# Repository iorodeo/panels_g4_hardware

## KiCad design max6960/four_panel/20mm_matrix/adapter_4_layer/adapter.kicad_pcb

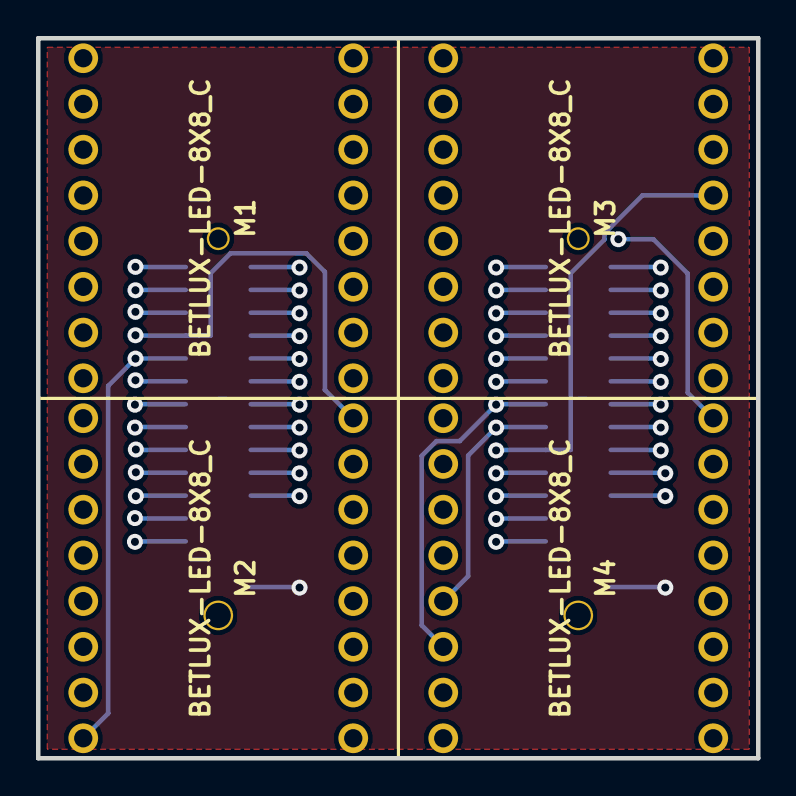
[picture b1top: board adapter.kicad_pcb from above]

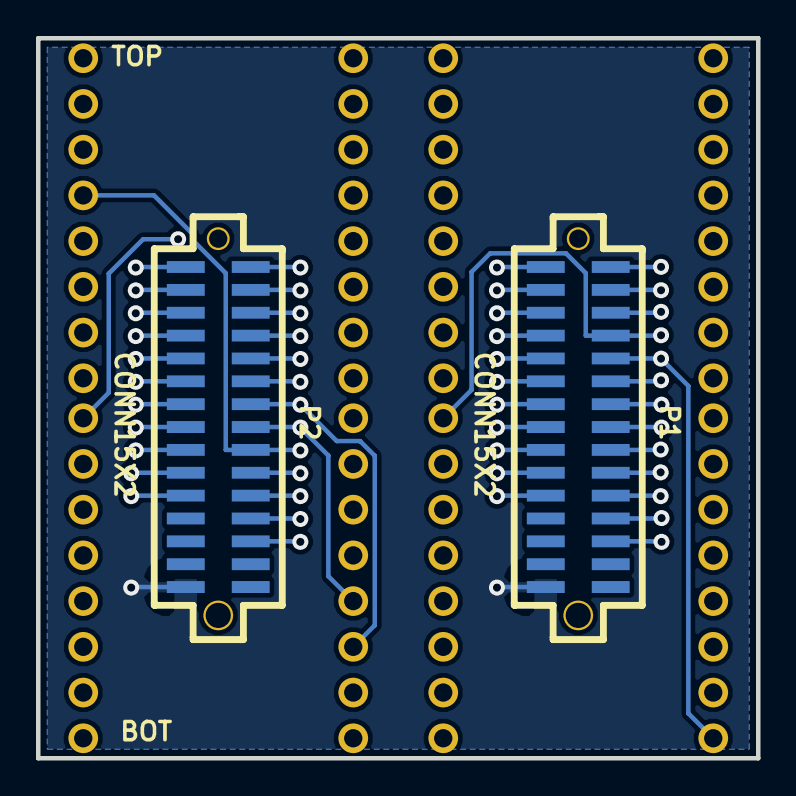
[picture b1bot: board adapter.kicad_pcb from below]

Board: 4 copper layers, 40.0 x 40.0 mm, 6 parts (2 on the bottom side), 49 nets.

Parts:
M1, M2, M3, M4: BETLUX-LED-8X8_C; LED_MATRIX_20MM_8x8
P1, P2: CONN15X2; SMD_PIN_ARRAY_F_0P5IN_15X2

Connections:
/COL_A1: M1.5, P1.18
/COL_A2: M1.6, P1.20
/COL_A3: M1.7, P1.22
/COL_A4: M1.8, P1.25
/COL_A5: M1.16, P1.23
/COL_A6: M1.15, P1.21
/COL_A7: M1.14, P1.19
/COL_A8: M1.13, P1.17
/COL_A9: M2.5, P1.15
/COL_A10: M2.6, P1.13
/COL_A11: M2.7, P1.11
/COL_A12: M2.8, P1.9
/COL_A13: M2.16, P1.7
/COL_A14: M2.15, P1.5
/COL_A15: M2.14, P1.3
/COL_A16: M2.13, P1.1
/COL_B1: M3.5, P2.18
/COL_B2: M3.6, P2.20
/COL_B3: M3.7, P2.22
/COL_B4: M3.8, P2.25
/COL_B5: M3.16, P2.23
/COL_B6: M3.15, P2.21
/COL_B7: M3.14, P2.19
/COL_B8: M3.13, P2.17
/COL_B9: M4.5, P2.15
/COL_B10: M4.6, P2.13
/COL_B11: M4.7, P2.11
/COL_B12: M4.8, P2.9
/COL_B13: M4.16, P2.7
/COL_B14: M4.15, P2.5
/COL_B15: M4.14, P2.3
/COL_B16: M4.13, P2.1
/ROW_A1: M1.1, M2.1, P1.2
/ROW_A2: M1.2, M2.2, P1.4
/ROW_A3: M1.3, M2.3, P1.6
/ROW_A4: M1.4, M2.4, P1.8
/ROW_A5: M1.12, M2.12, P1.10
/ROW_A6: M1.11, M2.11, P1.12
/ROW_A7: M1.10, M2.10, P1.14
/ROW_A8: M1.9, M2.9, P1.16
/ROW_B1: M3.1, M4.1, P2.2
/ROW_B2: M3.2, M4.2, P2.4
/ROW_B3: M3.3, M4.3, P2.6
/ROW_B4: M3.4, M4.4, P2.8
/ROW_B5: M3.12, M4.12, P2.10
/ROW_B6: M3.11, M4.11, P2.12
/ROW_B7: M3.10, M4.10, P2.14
/ROW_B8: M3.9, M4.9, P2.16
GND: P1.30, P2.30

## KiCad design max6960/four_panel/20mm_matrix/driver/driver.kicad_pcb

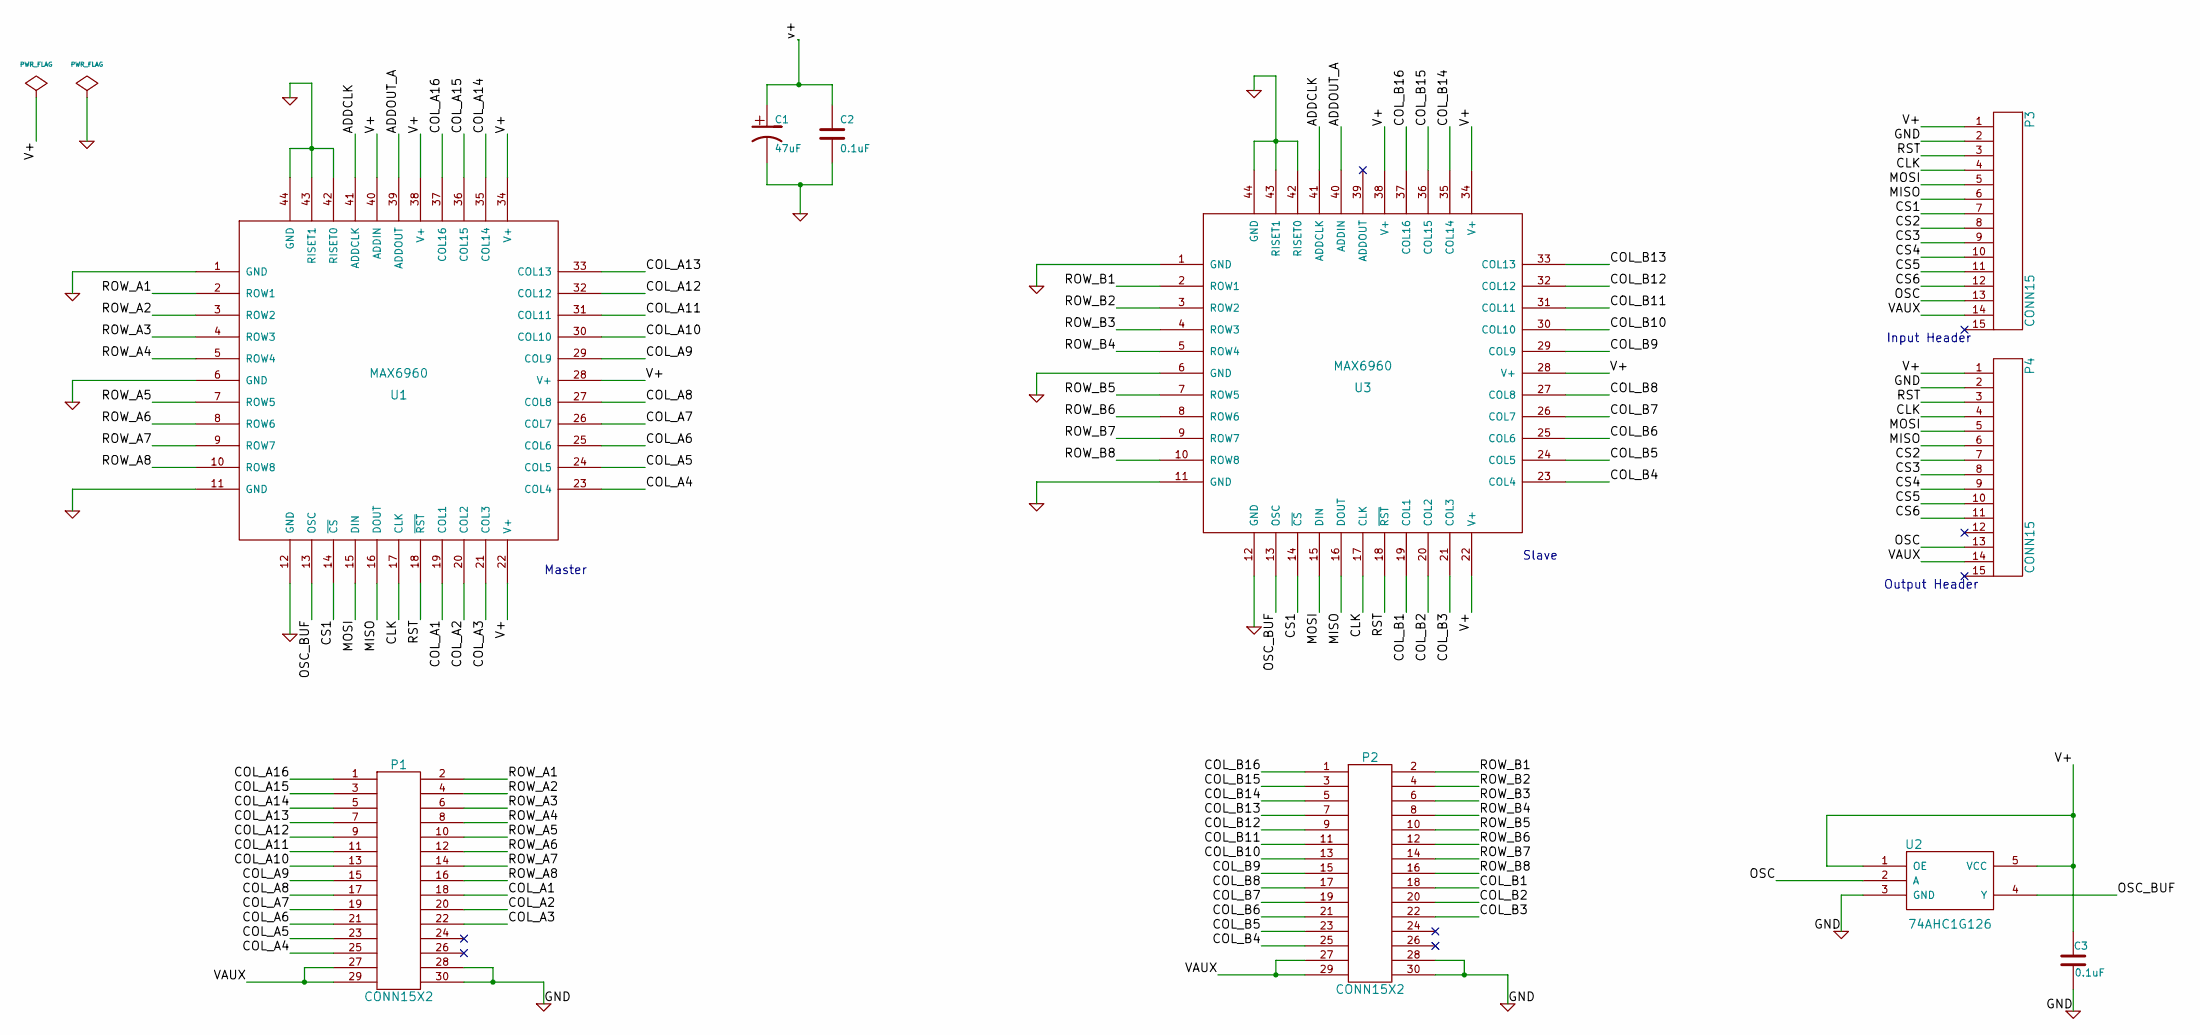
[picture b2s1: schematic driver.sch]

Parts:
C1: 47uF
C2, C3: 0.1uF
P1, P2: CONN15X2
P3, P4: CONN15
U1, U3: MAX6960
U2: 74AHC1G126

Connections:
/ADDCLK: U1.41 (ADDCLK), U3.41 (ADDCLK)
/ADDOUT_A: U1.39 (ADDOUT), U3.40 (ADDIN)
/CLK: P3.4, P4.4, U1.17 (CLK), U3.17 (CLK)
/COL_A1: P1.18, U1.19 (COL1)
/COL_A2: P1.20, U1.20 (COL2)
/COL_A3: P1.22, U1.21 (COL3)
/COL_A4: P1.25, U1.23 (COL4)
/COL_A5: P1.23, U1.24 (COL5)
/COL_A6: P1.21, U1.25 (COL6)
/COL_A7: P1.19, U1.26 (COL7)
/COL_A8: P1.17, U1.27 (COL8)
/COL_A9: P1.15, U1.29 (COL9)
/COL_A10: P1.13, U1.30 (COL10)
/COL_A11: P1.11, U1.31 (COL11)
/COL_A12: P1.9, U1.32 (COL12)
/COL_A13: P1.7, U1.33 (COL13)
/COL_A14: P1.5, U1.35 (COL14)
/COL_A15: P1.3, U1.36 (COL15)
/COL_A16: P1.1, U1.37 (COL16)
/COL_B1: P2.18, U3.19 (COL1)
/COL_B2: P2.20, U3.20 (COL2)
/COL_B3: P2.22, U3.21 (COL3)
/COL_B4: P2.25, U3.23 (COL4)
/COL_B5: P2.23, U3.24 (COL5)
/COL_B6: P2.21, U3.25 (COL6)
/COL_B7: P2.19, U3.26 (COL7)
/COL_B8: P2.17, U3.27 (COL8)
/COL_B9: P2.15, U3.29 (COL9)
/COL_B10: P2.13, U3.30 (COL10)
/COL_B11: P2.11, U3.31 (COL11)
/COL_B12: P2.9, U3.32 (COL12)
/COL_B13: P2.7, U3.33 (COL13)
/COL_B14: P2.5, U3.35 (COL14)
/COL_B15: P2.3, U3.36 (COL15)
/COL_B16: P2.1, U3.37 (COL16)
/CS1: P3.7, U1.14 (~CS), U3.14 (~CS)
/CS2: P3.8, P4.7
/CS3: P3.9, P4.8
/CS4: P3.10, P4.9
/CS5: P3.11, P4.10
/CS6: P3.12, P4.11
/MISO: P3.6, P4.6, U1.16 (DOUT), U3.16 (DOUT)
/MOSI: P3.5, P4.5, U1.15 (DIN), U3.15 (DIN)
/OSC: P3.13, P4.13, U2.2 (A)
/OSC_BUF: U1.13 (OSC), U2.4 (Y), U3.13 (OSC)
/ROW_A1: P1.2, U1.2 (ROW1)
/ROW_A2: P1.4, U1.3 (ROW2)
/ROW_A3: P1.6, U1.4 (ROW3)
/ROW_A4: P1.8, U1.5 (ROW4)
/ROW_A5: P1.10, U1.7 (ROW5)
/ROW_A6: P1.12, U1.8 (ROW6)
/ROW_A7: P1.14, U1.9 (ROW7)
/ROW_A8: P1.16, U1.10 (ROW8)
/ROW_B1: P2.2, U3.2 (ROW1)
/ROW_B2: P2.4, U3.3 (ROW2)
/ROW_B3: P2.6, U3.4 (ROW3)
/ROW_B4: P2.8, U3.5 (ROW4)
/ROW_B5: P2.10, U3.7 (ROW5)
/ROW_B6: P2.12, U3.8 (ROW6)
/ROW_B7: P2.14, U3.9 (ROW7)
/ROW_B8: P2.16, U3.10 (ROW8)
/RST: P3.3, P4.3, U1.18 (~RST), U3.18 (~RST)
/V+: C1.1, C2.1, C3.1, P3.1, P4.1, U1.22 (V+), U1.28 (V+), U1.34 (V+), U1.38 (V+), U1.40 (ADDIN), U2.1 (OE), U2.5 (VCC), U3.22 (V+), U3.28 (V+), U3.34 (V+), U3.38 (V+)
/VAUX: P1.27, P1.29, P2.27, P2.29, P3.14, P4.14
GND: C1.2, C2.2, C3.2, P1.28, P1.30, P2.28, P2.30, P3.2, P4.2, U1.1 (GND), U1.6 (GND), U1.11 (GND), U1.12 (GND), U1.42 (RISET0), U1.43 (RISET1), U1.44 (GND), U2.3 (GND), U3.1 (GND), U3.6 (GND), U3.11 (GND), U3.12 (GND), U3.42 (RISET0), U3.43 (RISET1), U3.44 (GND)

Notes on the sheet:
Slave
Master
Input Header
Output Header

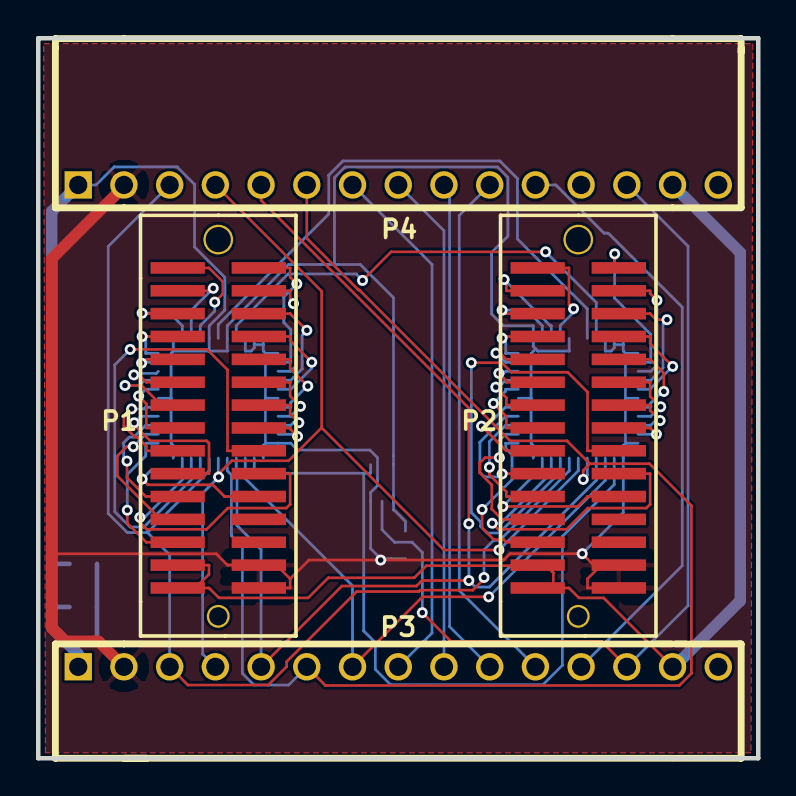
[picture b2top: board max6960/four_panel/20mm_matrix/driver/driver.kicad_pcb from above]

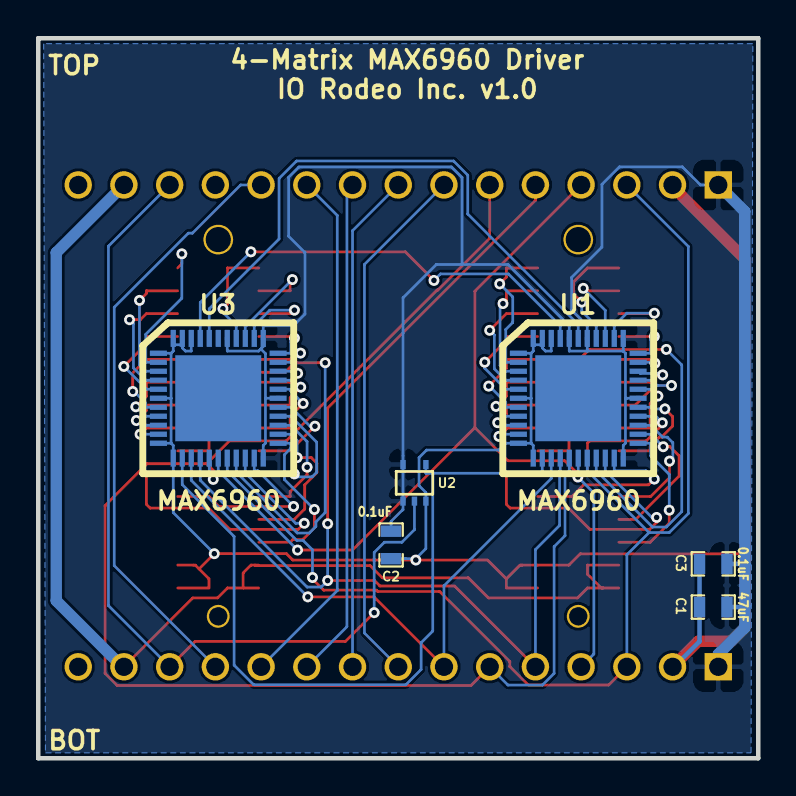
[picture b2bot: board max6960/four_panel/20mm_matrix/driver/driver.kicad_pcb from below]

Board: 2 copper layers, 40.0 x 40.0 mm, 10 parts (6 on the bottom side), 65 nets.

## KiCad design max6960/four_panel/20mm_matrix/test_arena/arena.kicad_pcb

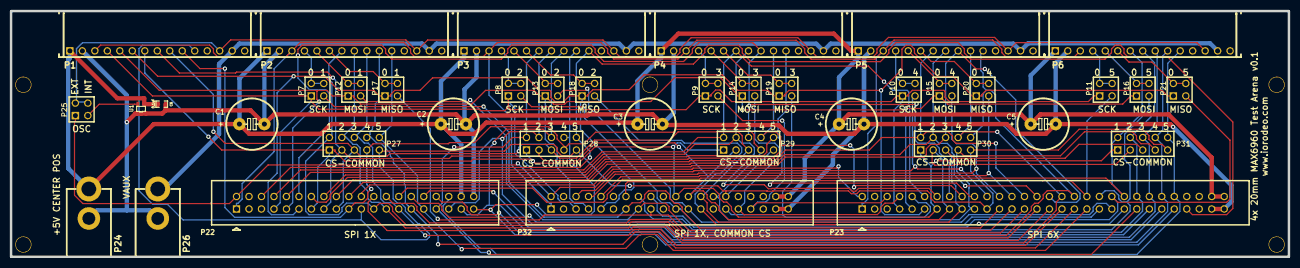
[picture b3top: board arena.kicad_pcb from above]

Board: 2 copper layers, 260.0 x 50.0 mm, 45 parts (0 on the bottom side), 70 nets.

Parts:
C1, C2, C3, C4, C5: 10uF; Capacitor_Polarized
C6: 0.1uF; SM0603_Capa
M1, M2, M3, M4, M5, M6: VAL**; MOUNT_HOLE_4_40
P1, P2, P3, P4, P5, P6: CONN15; HEADER_TOP
P7, P8, P9, P10, P11, P12, P13, P14, P15, P16, P17, P18, P19, P20, P21, P25: CONN_2X2; PIN_ARRAY_2X2
P22, P32: CONN_20X2; PIN_ARRAY_SHRD_20X2
P23: CONN_30X2; PIN_ARRAY_SHRD_30X2
P24, P26: CONN_2; DCJACK_2PIN
P27, P28, P29, P30, P31: CONN_5X2; PIN_ARRAY_5x2
U1: MAX7375; SOT323

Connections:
+3.3V: C1.1, C2.1, C3.1, C4.1, C5.1, C6.1, P1.1, P2.1, P3.1, P4.1, P5.1, P6.1, P22.38, P23.58, P23.60, P24.1, P32.38, P32.40, U1.1
/CLK_0: P1.4, P7.1, P8.1, P9.1, P10.1, P11.1, P22.7, P23.7, P32.5
/CLK_1: P7.3, P23.23, P32.13
/CLK_2: P8.3, P23.39, P32.21
/CLK_3: P9.3, P23.6, P32.33
/CLK_4: P10.3, P23.22, P32.6
/CLK_5: P11.3, P23.38, P32.14
/CLK_11: P2.4, P7.2, P7.4
/CLK_22: P3.4, P8.2, P8.4
/CLK_33: P4.4, P9.2, P9.4
/CLK_44: P5.4, P10.2, P10.4
/CLK_55: P6.4, P11.2, P11.4
/CS1_0: P1.7, P22.13, P23.13, P27.1, P28.1, P29.1, P30.1, P31.1, P32.22
/CS1_1: P2.7, P22.23, P23.29, P27.2
/CS1_2: P3.7, P22.33, P23.45, P28.2
/CS1_3: P4.7, P22.8, P23.12, P29.2
/CS1_4: P5.7, P22.18, P23.28, P30.2
/CS1_5: P6.7, P22.28, P23.44, P31.2
/CS2_0: P1.8, P22.15, P23.15, P27.3, P28.3, P29.3, P30.3, P31.3, P32.24
/CS2_1: P2.8, P22.25, P23.31, P27.4
/CS2_2: P3.8, P22.35, P23.47, P28.4
/CS2_3: P4.8, P22.10, P23.14, P29.4
/CS2_4: P5.8, P22.20, P23.30, P30.4
/CS2_5: P6.8, P22.30, P23.46, P31.4
/CS3_0: P1.9, P22.17, P23.17, P27.5, P28.5, P29.5, P30.5, P31.5, P32.26
/CS3_1: P2.9, P22.27, P23.33, P27.6
/CS3_2: P3.9, P22.37, P23.49, P28.6
/CS3_3: P4.9, P22.12, P23.16, P29.6
/CS3_4: P5.9, P22.22, P23.32, P30.6
/CS3_5: P6.9, P22.32, P23.48, P31.6
/CS4_0: P1.10, P22.19, P23.19, P27.7, P28.7, P29.7, P30.7, P31.7, P32.28
/CS4_1: P2.10, P22.29, P23.35, P27.8
/CS4_2: P3.10, P22.39, P23.51, P28.8
/CS4_3: P4.10, P22.14, P23.18, P29.8
/CS4_4: P5.10, P22.24, P23.34, P30.8
/CS4_5: P6.10, P22.34, P23.50, P31.8
/CS5_0: P1.11, P22.21, P23.21, P27.9, P28.9, P29.9, P30.9, P31.9, P32.30
/CS5_1: P2.11, P22.31, P23.37, P27.10
/CS5_2: P3.11, P22.6, P23.53, P28.10
/CS5_3: P4.11, P22.16, P23.20, P29.10
/CS5_4: P5.11, P22.26, P23.36, P30.10
/CS5_5: P6.11, P22.36, P23.52, P31.10
/MISO_0: P1.6, P17.1, P18.1, P19.1, P20.1, P21.1, P22.11, P23.11, P32.9
/MISO_1: P17.3, P23.27, P32.17
/MISO_2: P18.3, P23.43, P32.25
/MISO_3: P19.3, P23.10, P32.29
/MISO_4: P20.3, P23.26, P32.10
/MISO_5: P21.3, P23.42, P32.18
/MISO_11: P2.6, P17.2, P17.4
/MISO_22: P3.6, P18.2, P18.4
/MISO_33: P4.6, P19.2, P19.4
/MISO_44: P5.6, P20.2, P20.4
/MISO_55: P6.6, P21.2, P21.4
/MOSI_0: P1.5, P12.1, P13.1, P14.1, P15.1, P16.1, P22.9, P23.9, P32.7
/MOSI_1: P12.3, P23.25, P32.15
/MOSI_2: P13.3, P23.41, P32.23
/MOSI_3: P14.3, P23.8, P32.31
/MOSI_4: P15.3, P23.24, P32.8
/MOSI_5: P16.3, P23.40, P32.16
/MOSI_11: P2.5, P12.2, P12.4
/MOSI_22: P3.5, P13.2, P13.4
/MOSI_33: P4.5, P14.2, P14.4
/MOSI_44: P5.5, P15.2, P15.4
/MOSI_55: P6.5, P16.2, P16.4
/OSC: P1.13, P2.13, P3.13, P4.13, P5.13, P6.13, P25.2, P25.4
/OSC_EXT: P22.2, P23.2, P25.1, P32.2
/OSC_INT: P25.3, U1.2
/RST: P1.3, P2.3, P3.3, P4.3, P5.3, P6.3, P22.1, P23.1, P32.1
/VAUX: P1.14, P2.14, P3.14, P4.14, P5.14, P6.14, P26.1
GND: C1.2, C2.2, C3.2, C4.2, C5.2, C6.2, P1.2, P2.2, P3.2, P4.2, P5.2, P6.2, P22.40, P23.57, P23.59, P24.2, P26.2, P32.37, P32.39, U1.3

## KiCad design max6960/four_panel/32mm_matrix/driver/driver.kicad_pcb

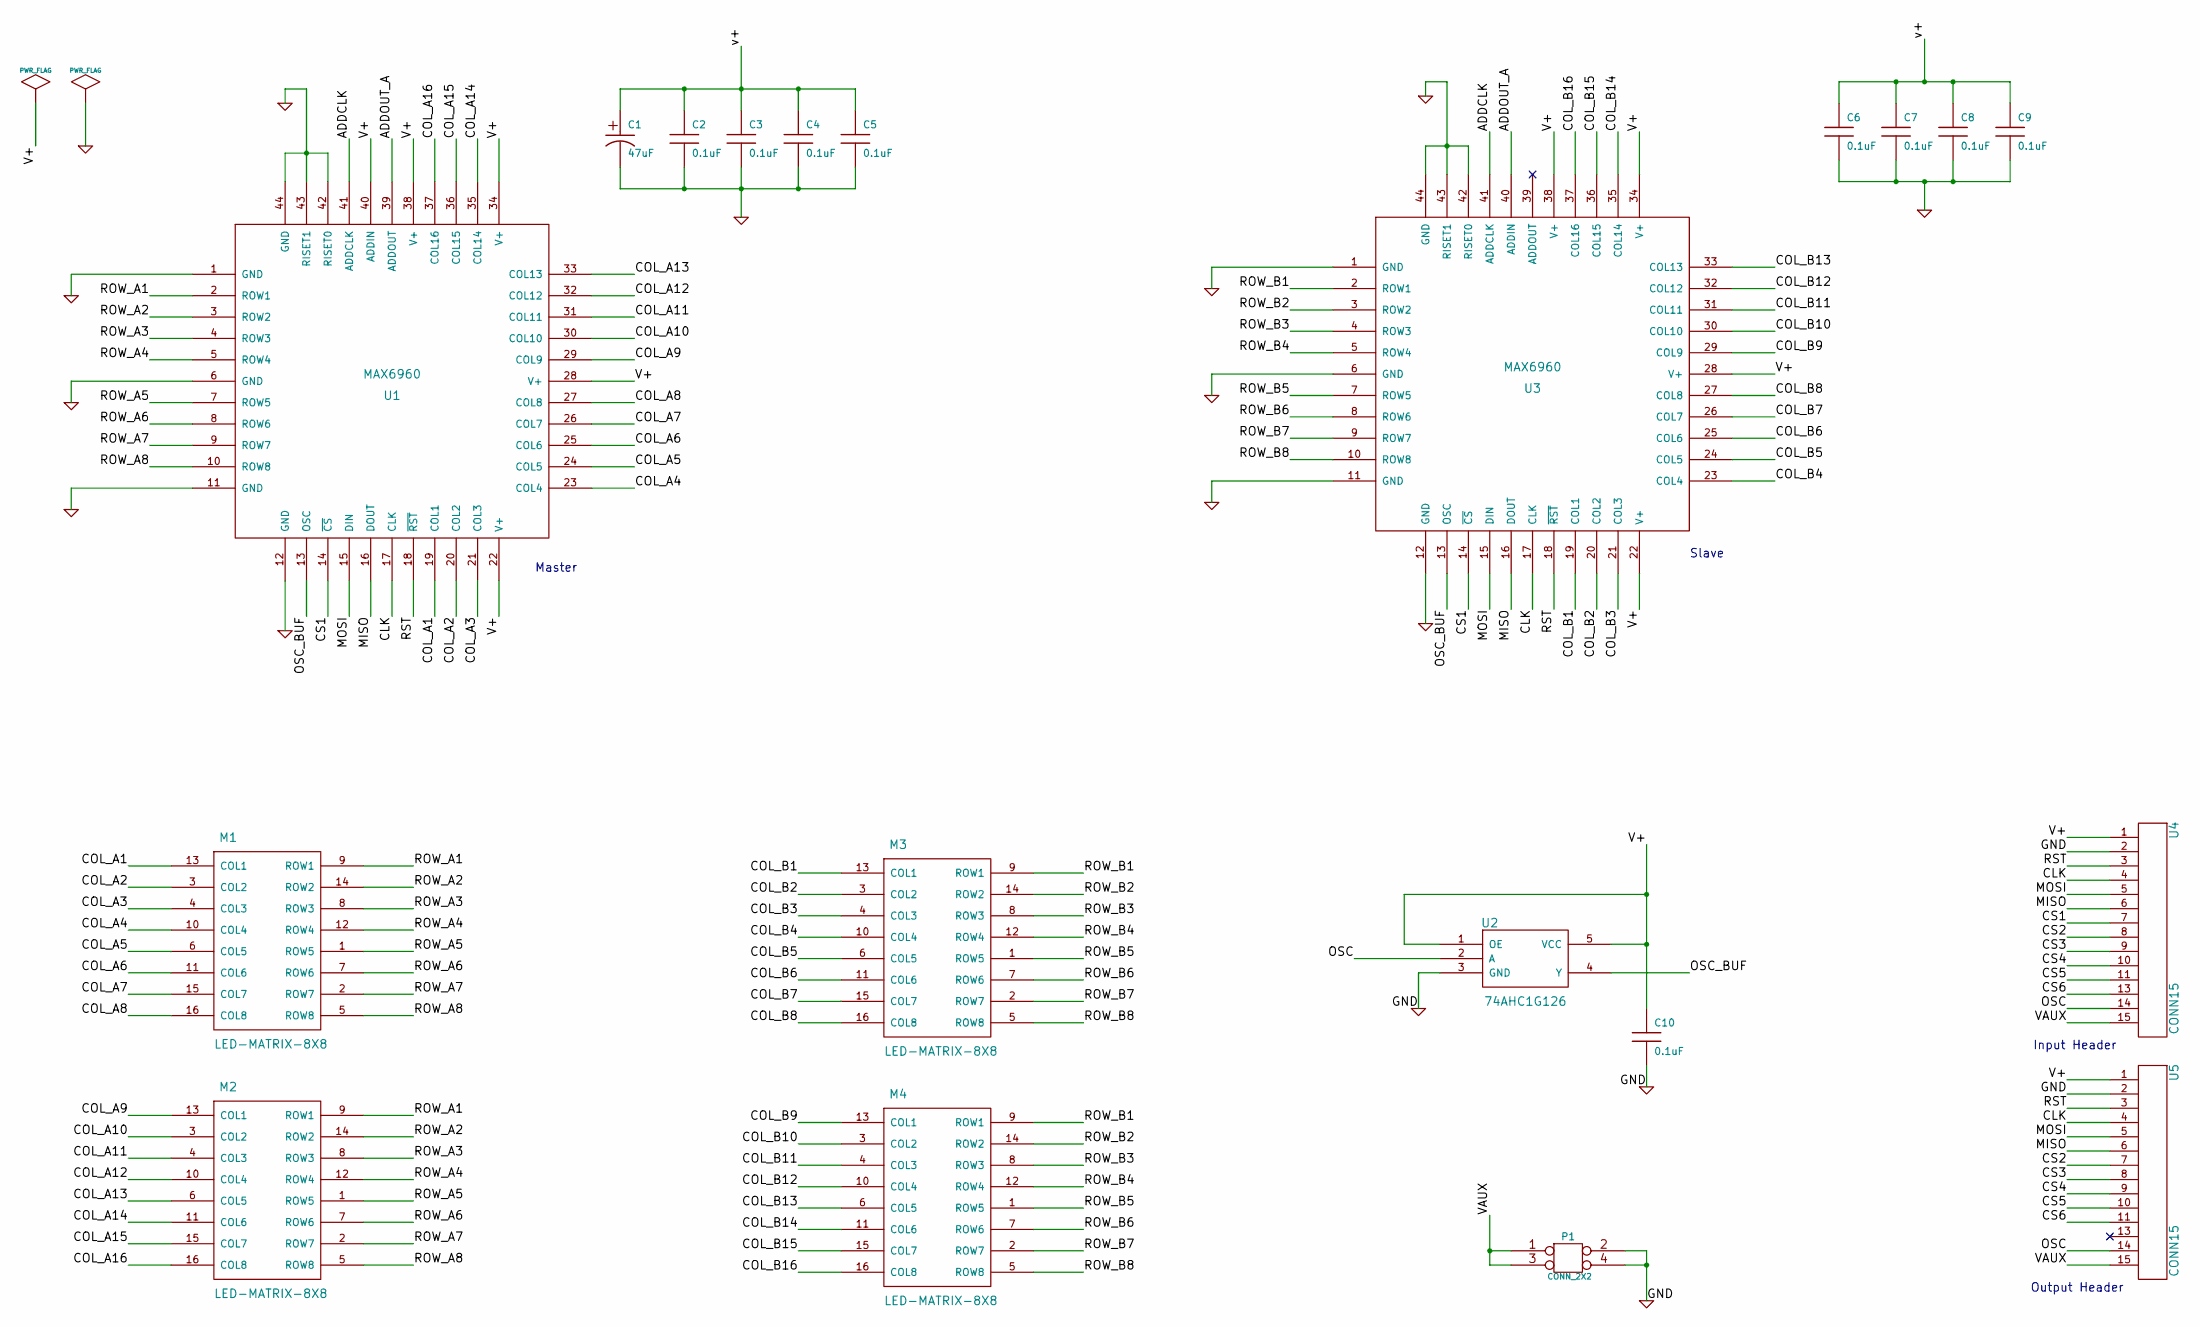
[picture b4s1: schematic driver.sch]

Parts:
C1: 47uF
C2, C3, C4, C5, C6, C7, C8, C9, C10: 0.1uF
M1, M2, M3, M4: LED-MATRIX-8X8
P1: CONN_2X2
U1, U3: MAX6960
U2: 74AHC1G126
U4, U5: CONN15

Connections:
/ADDCLK: U1.41 (ADDCLK), U3.41 (ADDCLK)
/ADDOUT_A: U1.39 (ADDOUT), U3.40 (ADDIN)
/CLK: U1.17 (CLK), U3.17 (CLK), U4.4, U5.4
/COL_A1: M1.13 (COL1), U1.19 (COL1)
/COL_A2: M1.3 (COL2), U1.20 (COL2)
/COL_A3: M1.4 (COL3), U1.21 (COL3)
/COL_A4: M1.10 (COL4), U1.23 (COL4)
/COL_A5: M1.6 (COL5), U1.24 (COL5)
/COL_A6: M1.11 (COL6), U1.25 (COL6)
/COL_A7: M1.15 (COL7), U1.26 (COL7)
/COL_A8: M1.16 (COL8), U1.27 (COL8)
/COL_A9: M2.13 (COL1), U1.29 (COL9)
/COL_A10: M2.3 (COL2), U1.30 (COL10)
/COL_A11: M2.4 (COL3), U1.31 (COL11)
/COL_A12: M2.10 (COL4), U1.32 (COL12)
/COL_A13: M2.6 (COL5), U1.33 (COL13)
/COL_A14: M2.11 (COL6), U1.35 (COL14)
/COL_A15: M2.15 (COL7), U1.36 (COL15)
/COL_A16: M2.16 (COL8), U1.37 (COL16)
/COL_B1: M3.13 (COL1), U3.19 (COL1)
/COL_B2: M3.3 (COL2), U3.20 (COL2)
/COL_B3: M3.4 (COL3), U3.21 (COL3)
/COL_B4: M3.10 (COL4), U3.23 (COL4)
/COL_B5: M3.6 (COL5), U3.24 (COL5)
/COL_B6: M3.11 (COL6), U3.25 (COL6)
/COL_B7: M3.15 (COL7), U3.26 (COL7)
/COL_B8: M3.16 (COL8), U3.27 (COL8)
/COL_B9: M4.13 (COL1), U3.29 (COL9)
/COL_B10: M4.3 (COL2), U3.30 (COL10)
/COL_B11: M4.4 (COL3), U3.31 (COL11)
/COL_B12: M4.10 (COL4), U3.32 (COL12)
/COL_B13: M4.6 (COL5), U3.33 (COL13)
/COL_B14: M4.11 (COL6), U3.35 (COL14)
/COL_B15: M4.15 (COL7), U3.36 (COL15)
/COL_B16: M4.16 (COL8), U3.37 (COL16)
/CS1: U1.14 (~CS), U3.14 (~CS), U4.7
/CS2: U4.8, U5.7
/CS3: U4.9, U5.8
/CS4: U4.10, U5.9
/CS5: U4.11, U5.10
/CS6: U4.13, U5.11
/MISO: U1.16 (DOUT), U3.16 (DOUT), U4.6, U5.6
/MOSI: U1.15 (DIN), U3.15 (DIN), U4.5, U5.5
/OSC: U2.2 (A), U4.14, U5.14
/OSC_BUF: U1.13 (OSC), U2.4 (Y), U3.13 (OSC)
/ROW_A1: M1.9 (ROW1), M2.9 (ROW1), U1.2 (ROW1)
/ROW_A2: M1.14 (ROW2), M2.14 (ROW2), U1.3 (ROW2)
/ROW_A3: M1.8 (ROW3), M2.8 (ROW3), U1.4 (ROW3)
/ROW_A4: M1.12 (ROW4), M2.12 (ROW4), U1.5 (ROW4)
/ROW_A5: M1.1 (ROW5), M2.1 (ROW5), U1.7 (ROW5)
/ROW_A6: M1.7 (ROW6), M2.7 (ROW6), U1.8 (ROW6)
/ROW_A7: M1.2 (ROW7), M2.2 (ROW7), U1.9 (ROW7)
/ROW_A8: M1.5 (ROW8), M2.5 (ROW8), U1.10 (ROW8)
/ROW_B1: M3.9 (ROW1), M4.9 (ROW1), U3.2 (ROW1)
/ROW_B2: M3.14 (ROW2), M4.14 (ROW2), U3.3 (ROW2)
/ROW_B3: M3.8 (ROW3), M4.8 (ROW3), U3.4 (ROW3)
/ROW_B4: M3.12 (ROW4), M4.12 (ROW4), U3.5 (ROW4)
/ROW_B5: M3.1 (ROW5), M4.1 (ROW5), U3.7 (ROW5)
/ROW_B6: M3.7 (ROW6), M4.7 (ROW6), U3.8 (ROW6)
/ROW_B7: M3.2 (ROW7), M4.2 (ROW7), U3.9 (ROW7)
/ROW_B8: M3.5 (ROW8), M4.5 (ROW8), U3.10 (ROW8)
/RST: U1.18 (~RST), U3.18 (~RST), U4.3, U5.3
/V+: C1.1, C2.1, C3.1, C4.1, C5.1, C6.1, C7.1, C8.1, C9.1, C10.1, U1.22 (V+), U1.28 (V+), U1.34 (V+), U1.38 (V+), U1.40 (ADDIN), U2.1 (OE), U2.5 (VCC), U3.22 (V+), U3.28 (V+), U3.34 (V+), U3.38 (V+), U4.1, U5.1
/VAUX: P1.1, P1.3, U4.15, U5.15
GND: C1.2, C2.2, C3.2, C4.2, C5.2, C6.2, C7.2, C8.2, C9.2, C10.2, P1.2, P1.4, U1.1 (GND), U1.6 (GND), U1.11 (GND), U1.12 (GND), U1.42 (RISET0), U1.43 (RISET1), U1.44 (GND), U2.3 (GND), U3.1 (GND), U3.6 (GND), U3.11 (GND), U3.12 (GND), U3.42 (RISET0), U3.43 (RISET1), U3.44 (GND), U4.2, U5.2

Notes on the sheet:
Slave
Master
Input Header
Output Header

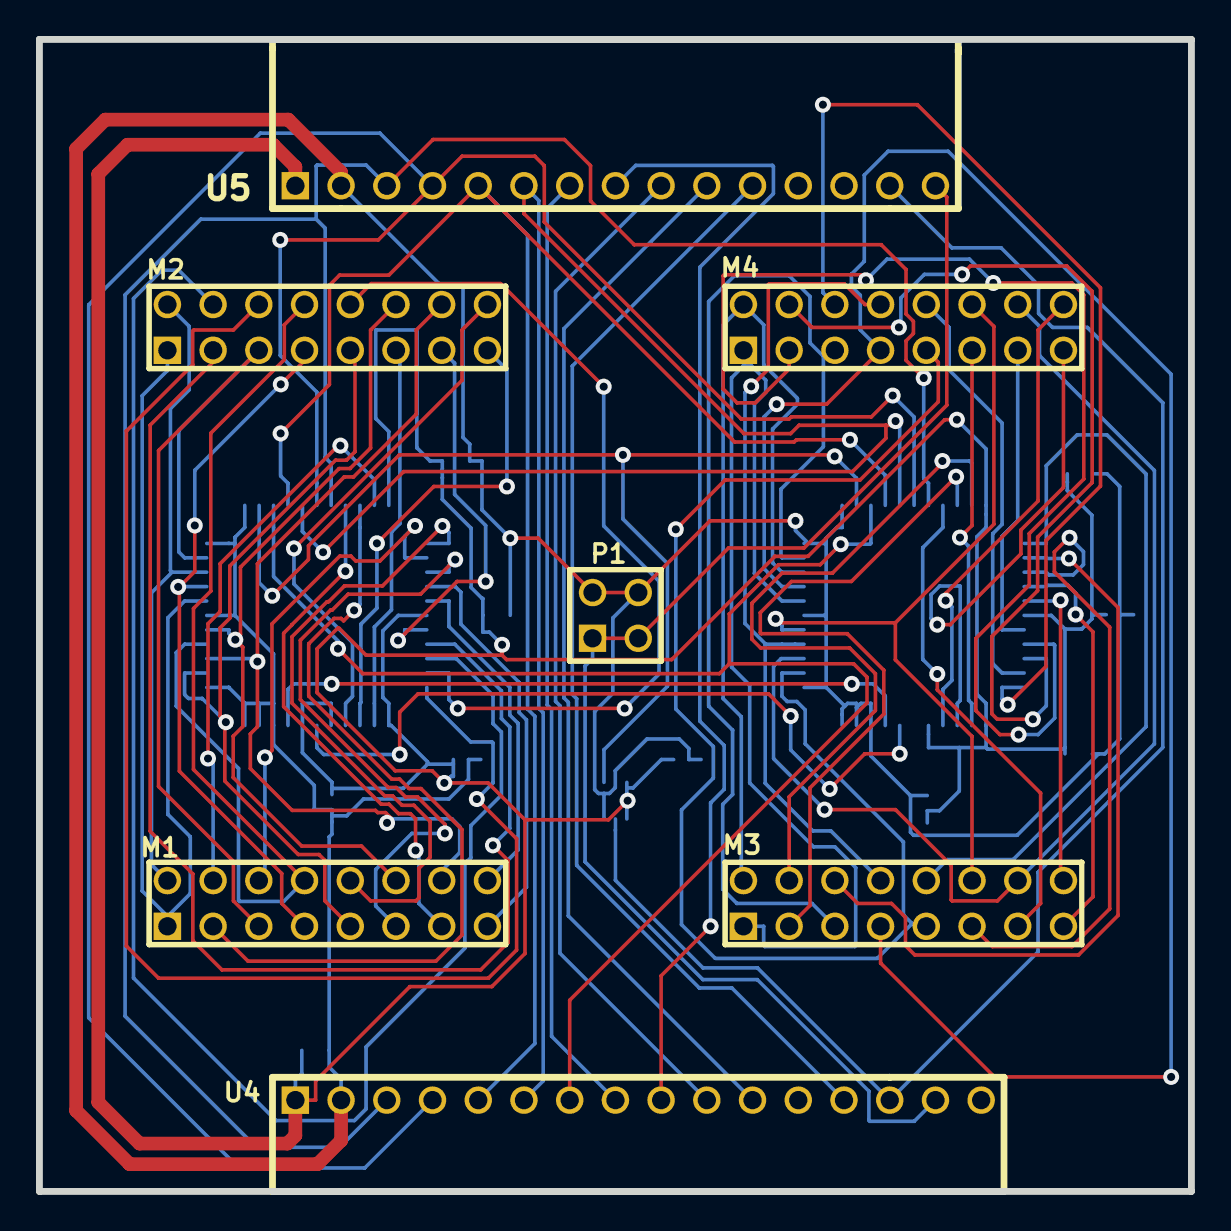
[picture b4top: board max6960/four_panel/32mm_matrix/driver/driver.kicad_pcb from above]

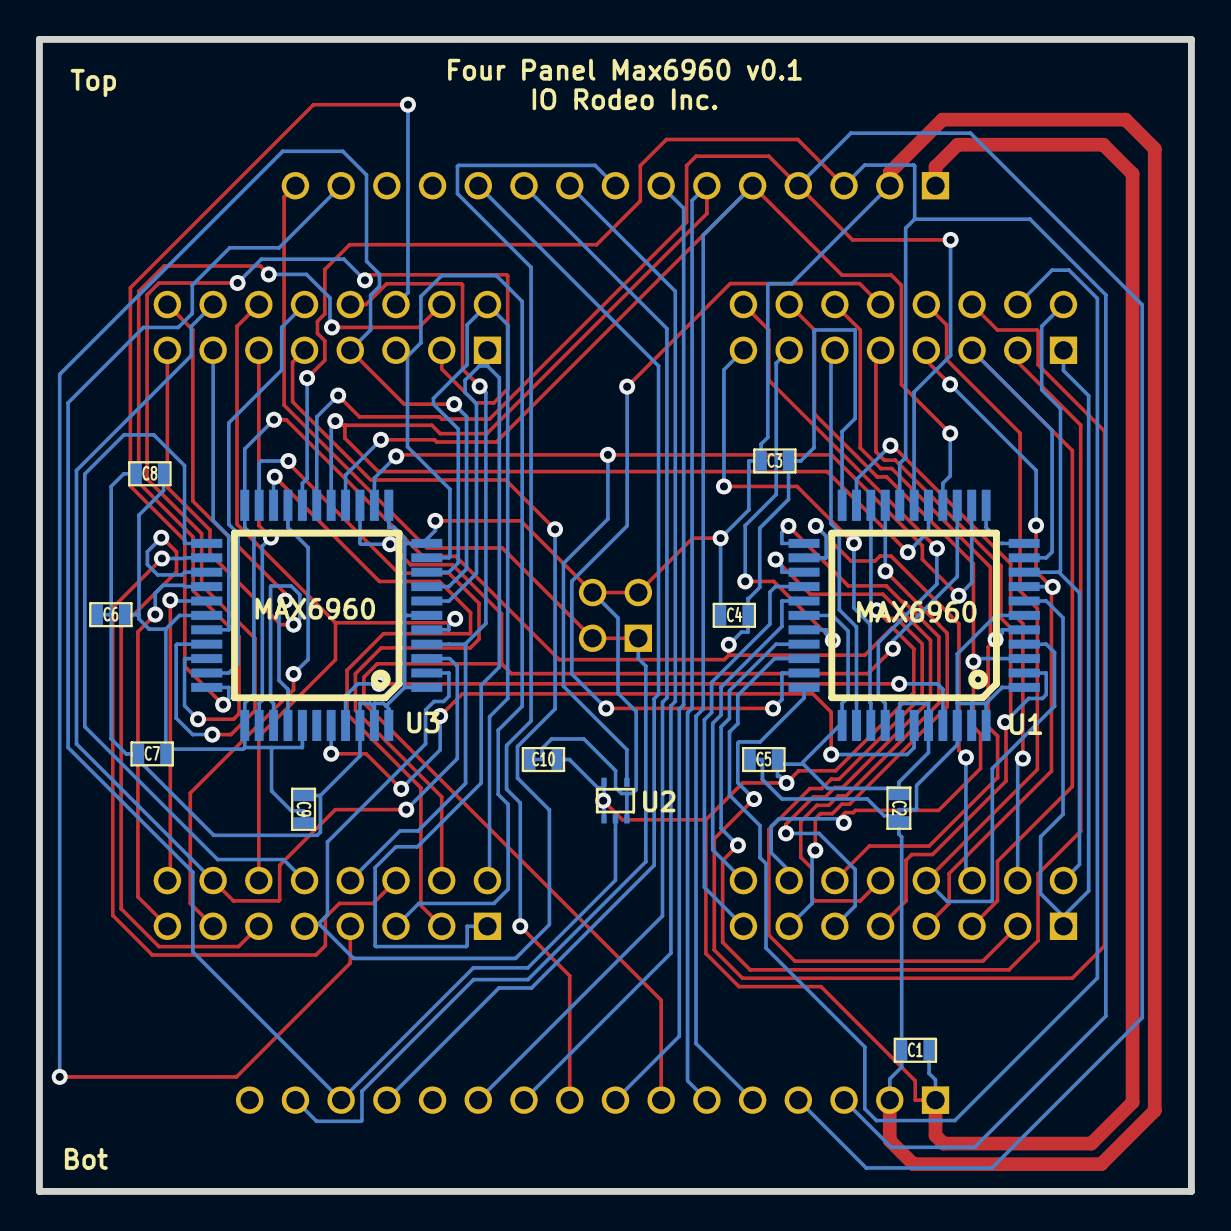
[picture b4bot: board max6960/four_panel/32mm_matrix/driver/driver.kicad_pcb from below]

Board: 2 copper layers, 64.0 x 64.0 mm, 20 parts (13 on the bottom side), 65 nets.

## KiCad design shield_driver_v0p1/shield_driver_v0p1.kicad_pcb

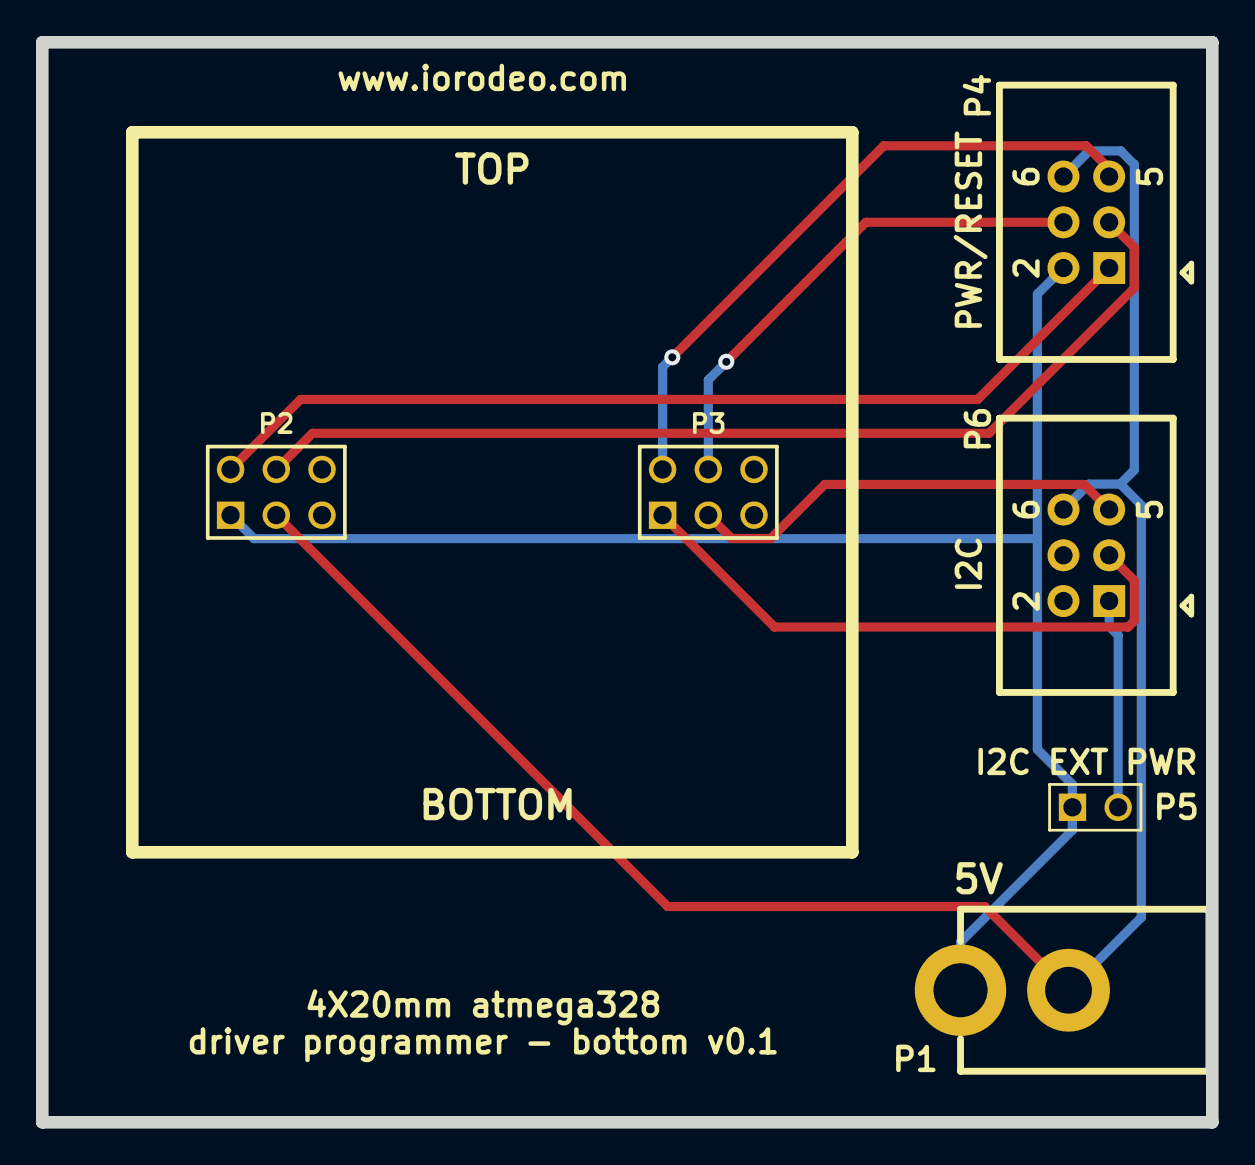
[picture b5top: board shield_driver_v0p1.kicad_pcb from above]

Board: 2 copper layers, 65.0 x 60.0 mm, 6 parts (0 on the bottom side), 9 nets.

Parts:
P1: CONN_2; DCJACK_2PIN
P2, P3: CONN_3X2; pin_array_3x2
P4, P6: CONN_3X2; 3X2_SHRD_HEADER
P5: CONN_2; PIN_ARRAY_2X1

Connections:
+5V: P1.1, P2.1, P4.2, P5.1
/SCL: P3.3, P6.5
/SDA: P3.1, P6.3
/~RST_1: P2.2, P4.1
/~RST_2: P2.4, P4.3
/~RST_3: P3.2, P4.5
/~RST_4: P3.4, P4.4
GND: P1.2, P2.3, P4.6, P6.6
unnamed: P5.2, P6.1

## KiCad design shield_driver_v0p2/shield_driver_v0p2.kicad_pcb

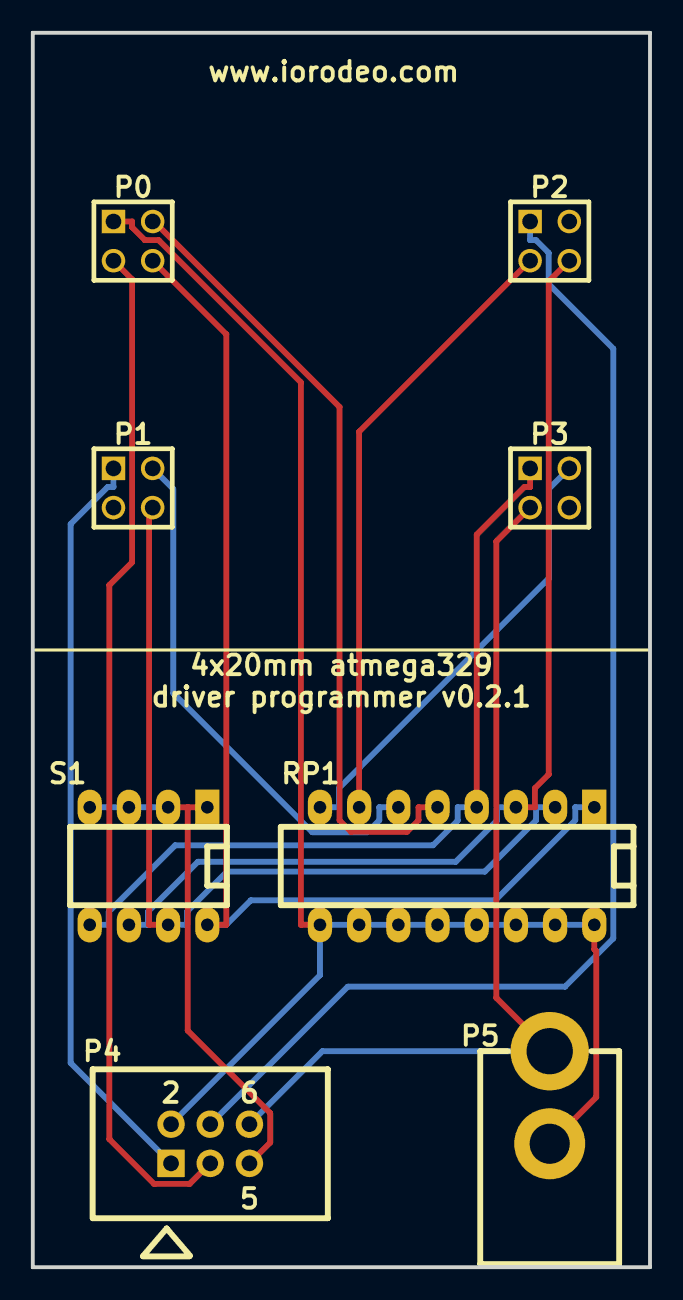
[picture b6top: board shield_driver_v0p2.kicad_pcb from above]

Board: 2 copper layers, 40.0 x 80.0 mm, 8 parts (0 on the bottom side), 14 nets.

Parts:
P0, P1, P2, P3: CONN_2X2; PIN_ARRAY_2X2
P4: CONN_3X2; 3X2_SHRD_HEADER
P5: CONN_2; DCJACK_2PIN
RP1: R_PACK8; DIP-16__300_ELL
S1: DIP_SWITCH_4; DIP-8__300_ELL

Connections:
+5V: P0.1, P4.2, P5.2, RP1.9, RP1.10, RP1.11, RP1.12, RP1.13, RP1.14, RP1.15, RP1.16
/CS0: P0.2, RP1.5
/CS1: P1.2, RP1.6
/CS2: P2.3, RP1.7
/CS3: P3.2, RP1.8
/MISO: P1.1, P4.1
/MOSI: P2.1, P4.4
/RESET: P4.5, S1.1, S1.2, S1.3, S1.4
/RESET_DRV0: P0.4, RP1.1, S1.8
/RESET_DRV1: P1.4, RP1.2, S1.7
/RESET_DRV2: P2.4, RP1.3, S1.6
/RESET_DRV3: P3.1, RP1.4, S1.5
/SCK: P0.3, P4.3
GND: P3.3, P4.6, P5.1
